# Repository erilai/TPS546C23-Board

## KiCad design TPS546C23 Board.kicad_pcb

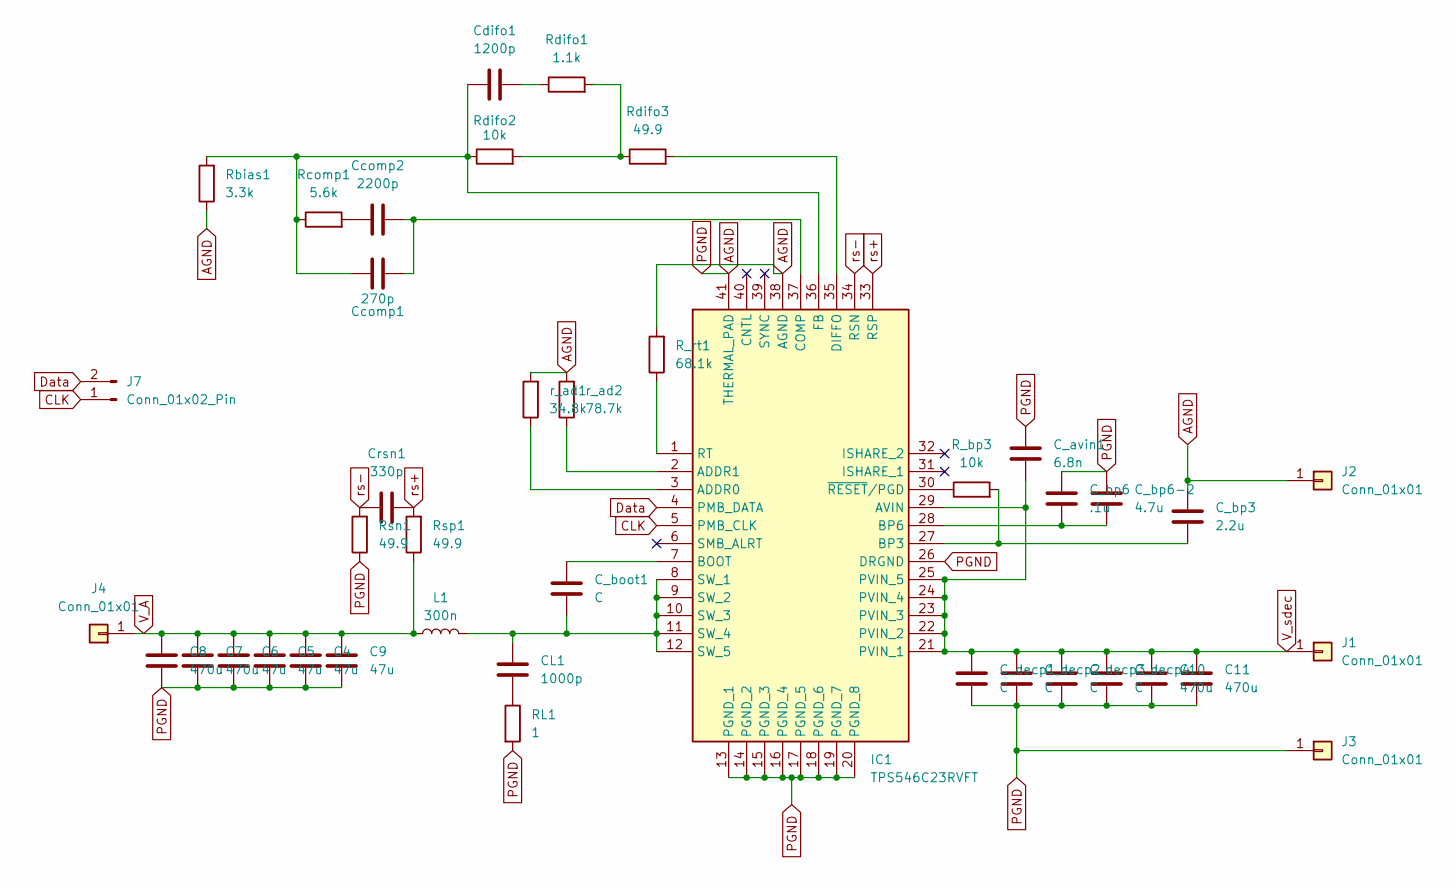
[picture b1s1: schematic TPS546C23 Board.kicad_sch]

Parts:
C4, C5, C6, C9: 47u; C_0805_2012Metric
C7, C8, C10, C11: 470u; CP_Elec_6.3x7.7
CL1: 1000p; C_0402_1005Metric
C_avin1: 6.8n; C_0402_1005Metric
C_boot1: C; C_0402_1005Metric
C_bp3: 2.2u; C_0402_1005Metric
C_bp6: .1u; C_0402_1005Metric
C_bp6-2: 4.7u; C_0402_1005Metric
C_decp1, C_decp2, C_decp3, C_decp4: C; C_0402_1005Metric
Ccomp1: 270p; C_0402_1005Metric
Ccomp2: 2200p; C_0402_1005Metric
Cdifo1: 1200p; C_0402_1005Metric
Crsn1: 330p; C_0402_1005Metric
IC1: TPS546C23RVFT; QFN50P500X700X152-41N-D; Mouser Part Number 595-TPS546C23RVFT
J1, J2, J3, J4: Conn_01x01; CalTest_CT3151
J7: Conn_01x02_Pin; PinHeader_1x02_P2.54mm_Vertical
L1: 300n; L_Sunlord_MWSA1204S-1R0
RL1: 1; R_0402_1005Metric
R_bp3: 10k; R_0402_1005Metric
R_rt1: 68.1k; R_0402_1005Metric
Rbias1: 3.3k; R_0402_1005Metric
Rcomp1: 5.6k; R_0402_1005Metric
Rdifo1: 1.1k; R_0402_1005Metric
Rdifo2: 10k; R_0402_1005Metric
Rdifo3: 49.9; R_0402_1005Metric
Rsn1: 49.9; R_0402_1005Metric
Rsp1: 49.9; R_0402_1005Metric
r_ad1: 34.8k; R_0402_1005Metric
r_ad2: 78.7k; R_0402_1005Metric

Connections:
AGND: C4.2, C5.2, C6.2, C7.2, C8.2, C9.2, C10.2, C11.2, C_avin1.1, C_bp3.1, C_bp6.1, C_bp6-2.1, C_decp1.2, C_decp2.2, C_decp3.2, C_decp4.2, IC1.13 (PGND_1), IC1.14 (PGND_2), IC1.15 (PGND_3), IC1.16 (PGND_4), IC1.17 (PGND_5), IC1.18 (PGND_6), IC1.19 (PGND_7), IC1.20 (PGND_8), IC1.26 (DRGND), IC1.38 (AGND), IC1.41 (THERMAL_PAD), J2.1 (Pin_1_1), J3.1 (Pin_1_1), RL1.2, R_rt1.2, Rbias1.1, Rsn1.1, r_ad1.2, r_ad2.2
CLK: IC1.5 (PMB_CLK), J7.1
Data: IC1.4 (PMB_DATA), J7.2
unnamed: CL1.2, RL1.1
unnamed: Ccomp2.2, Rcomp1.2
unnamed: Cdifo1.1, Rdifo1.1
unnamed: IC1.3 (ADDR0), r_ad1.1
unnamed: IC1.2 (ADDR1), r_ad2.1
unnamed: C_boot1.1, IC1.7 (BOOT)
unnamed: C_bp3.2, IC1.27 (BP3), R_bp3.2
unnamed: C_bp6.2, C_bp6-2.2, IC1.28 (BP6)
unnamed: Ccomp1.1, Ccomp2.1, IC1.37 (COMP)
unnamed: IC1.35 (DIFFO), Rdifo3.2
unnamed: Ccomp1.2, Cdifo1.2, IC1.36 (FB), Rbias1.2, Rcomp1.1, Rdifo2.1
unnamed: IC1.1 (RT), R_rt1.1
unnamed: CL1.1, C_boot1.2, IC1.8 (SW_1), IC1.9 (SW_2), IC1.10 (SW_3), IC1.11 (SW_4), IC1.12 (SW_5), L1.2
unnamed: IC1.30 (~RESET/PGD), R_bp3.1
unnamed: Rdifo1.2, Rdifo2.2, Rdifo3.1
V_A: C4.1, C5.1, C6.1, C7.1, C8.1, C9.1, J4.1 (Pin_1_1), L1.1, Rsp1.1
V_sdec: C10.1, C11.1, C_avin1.2, C_decp1.1, C_decp2.1, C_decp3.1, C_decp4.1, IC1.21 (PVIN_1), IC1.22 (PVIN_2), IC1.23 (PVIN_3), IC1.24 (PVIN_4), IC1.25 (PVIN_5), IC1.29 (AVIN), J1.1 (Pin_1_1)
rs+: Crsn1.2, IC1.33 (RSP), Rsp1.2
rs-: Crsn1.1, IC1.34 (RSN), Rsn1.2

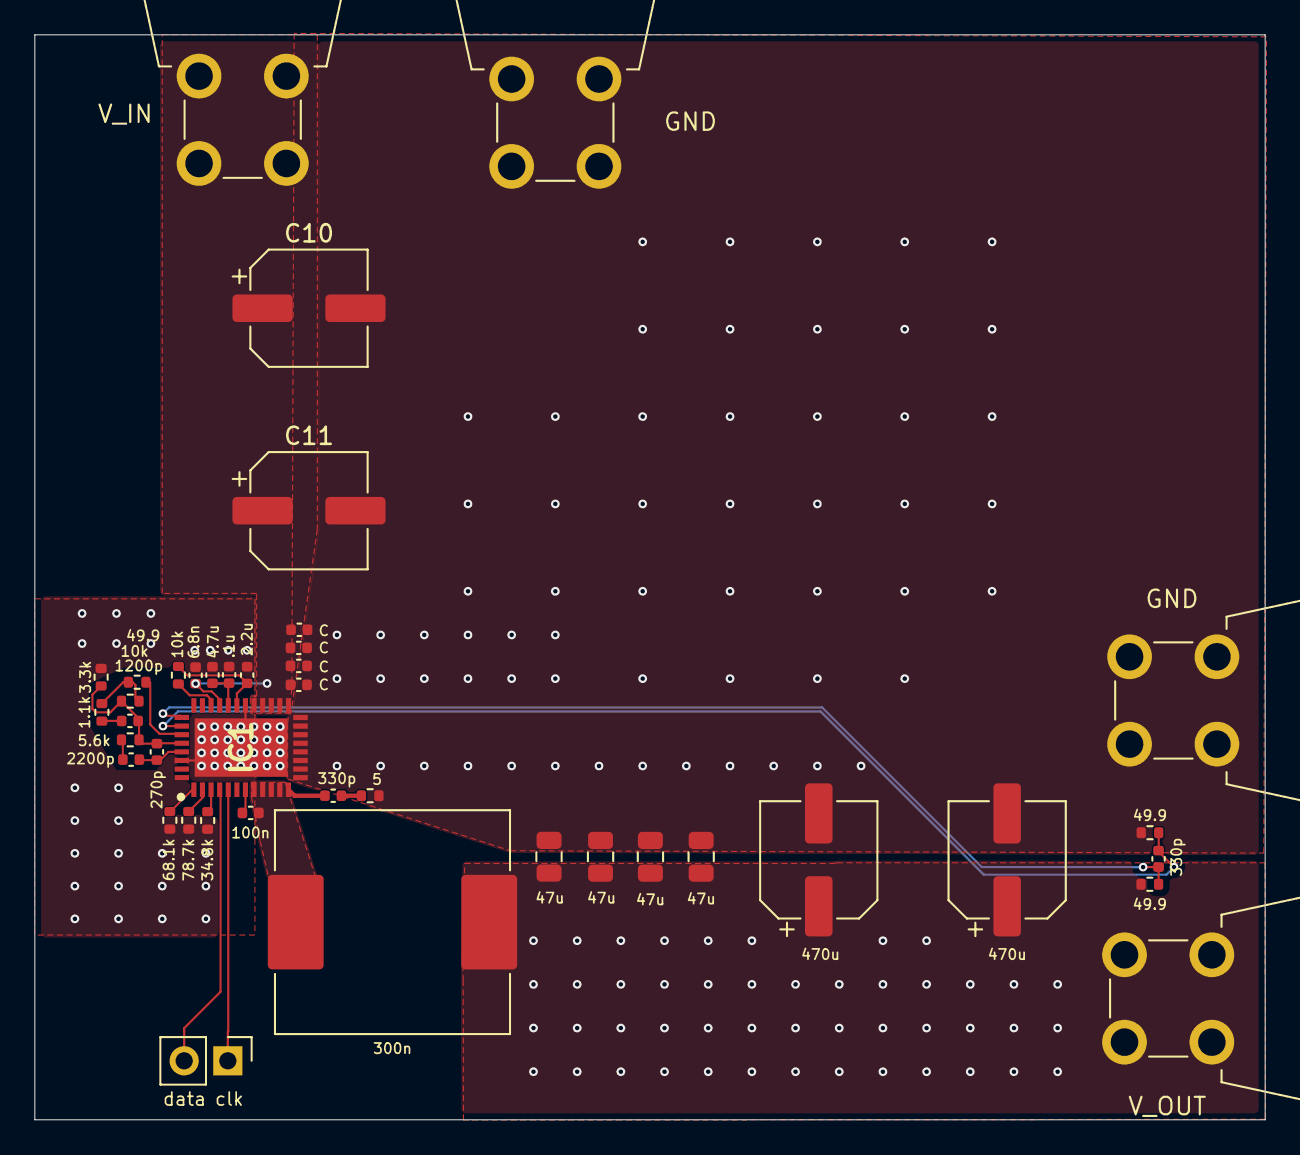
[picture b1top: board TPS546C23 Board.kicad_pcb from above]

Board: 4 copper layers, 71.6 x 63.1 mm, 41 parts (0 on the bottom side), 22 nets.

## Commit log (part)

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2026-06-25 final
2026-06-25 add fp and sym, it wasnt final
2026-06-25 drc fixes
2026-06-25 text fixes
